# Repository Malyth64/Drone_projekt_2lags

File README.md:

# Drone_projekt_2lags
to lags ECS

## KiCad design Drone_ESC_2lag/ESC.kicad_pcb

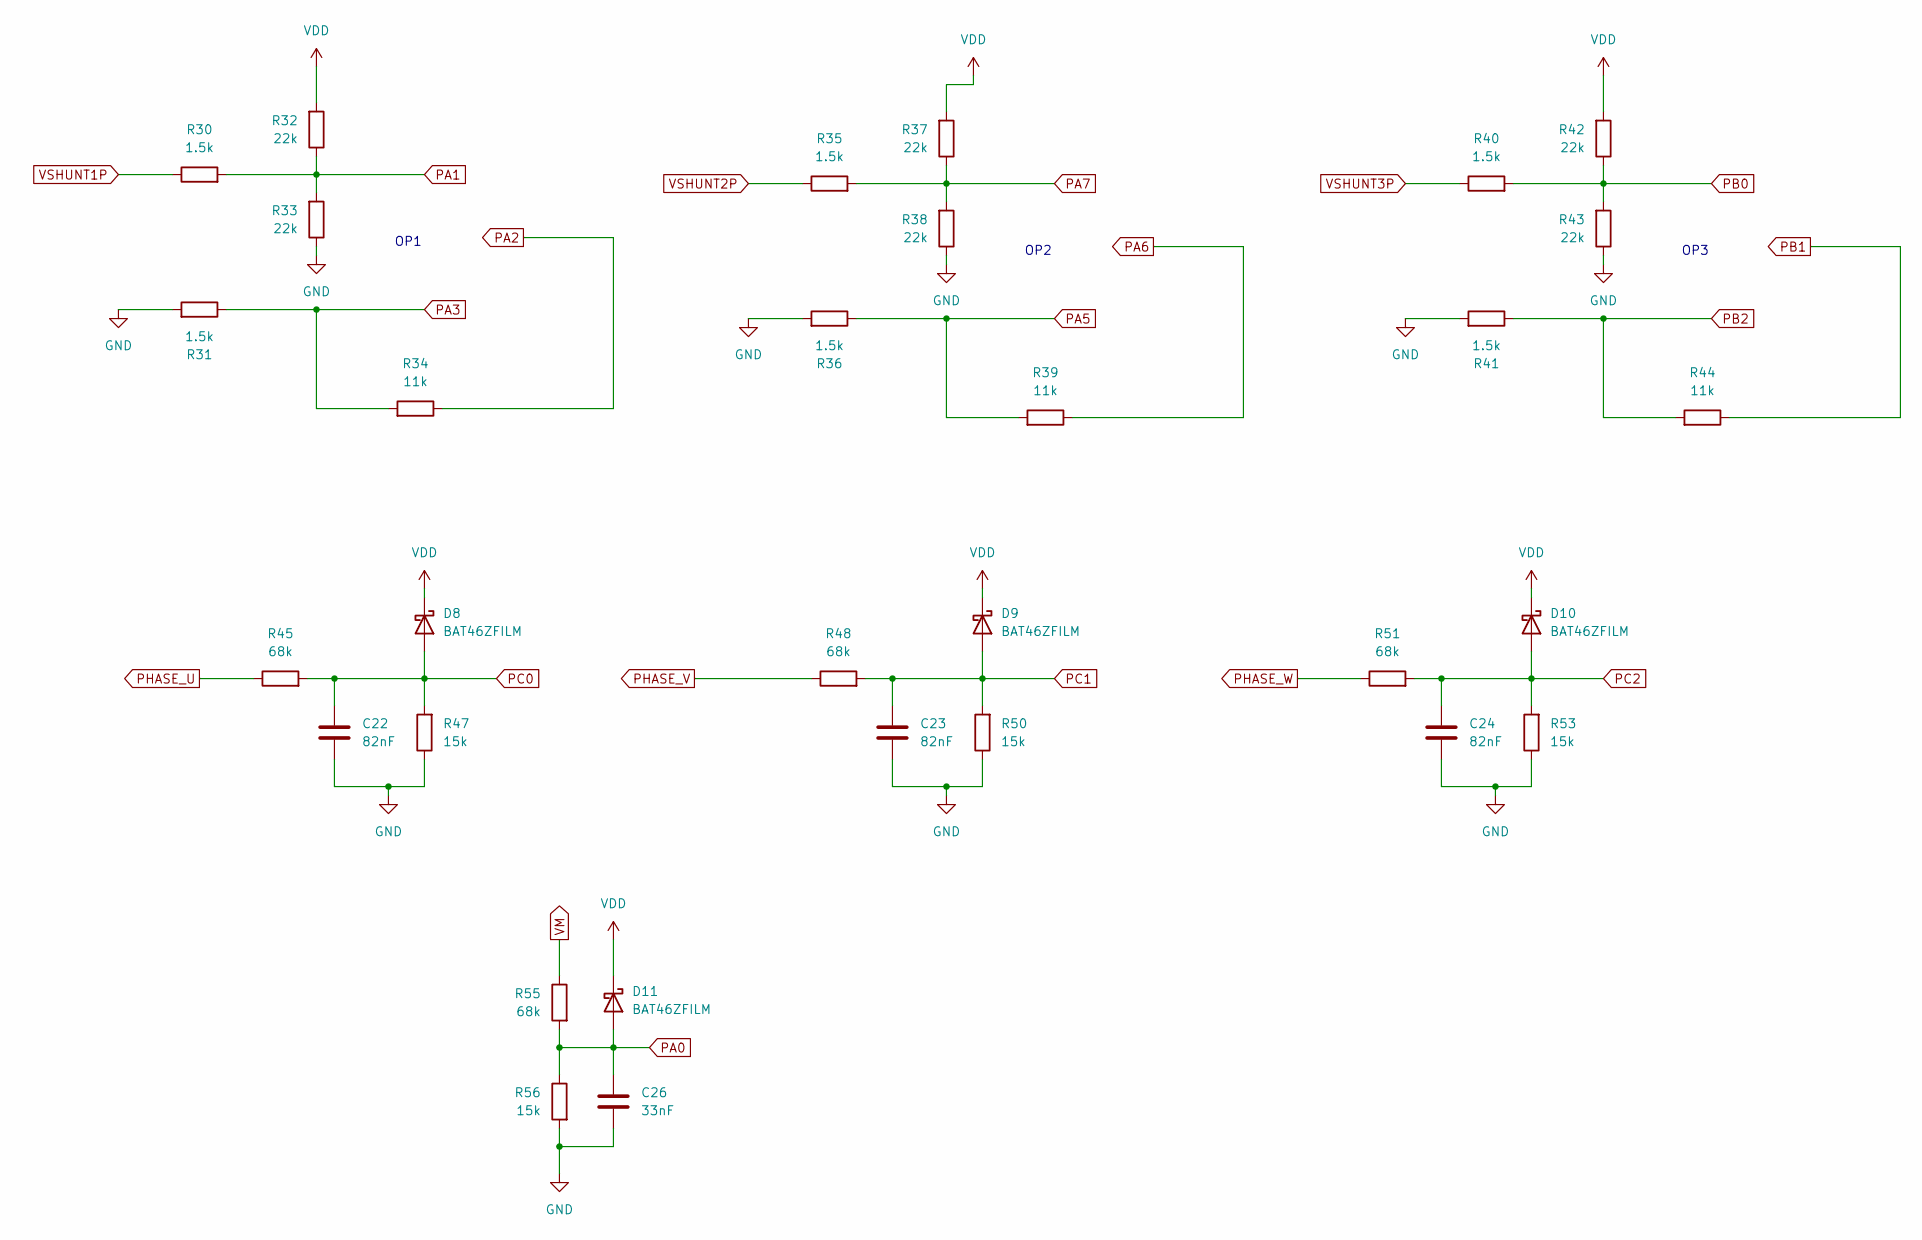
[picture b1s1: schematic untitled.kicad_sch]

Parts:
C22, C23, C24: 82nF; C_0805_2012Metric_Pad1.18x1.45mm_HandSolder
C26: 33nF; C_0805_2012Metric_Pad1.18x1.45mm_HandSolder
D8, D9, D10, D11: BAT46ZFILM; D_SOD-123
R30, R31, R35, R36, R40, R41: 1.5k; R_0805_2012Metric_Pad1.20x1.40mm_HandSolder
R32, R33, R37, R38, R42, R43: 22k; R_0805_2012Metric_Pad1.20x1.40mm_HandSolder
R34, R39, R44: 11k; R_0805_2012Metric_Pad1.20x1.40mm_HandSolder
R45, R48, R51: 68k; R_0805_2012Metric_Pad1.20x1.40mm_HandSolder
R47, R50, R53, R56: 15k; R_0805_2012Metric_Pad1.20x1.40mm_HandSolder
R55: 68k; R_0603_1608Metric_Pad0.98x0.95mm_HandSolder

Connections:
GND: C22.2, C23.2, C24.2, C26.2, R31.2, R33.1, R36.2, R38.1, R41.2, R43.1, R47.1, R50.1, R53.1, R56.2; also elsewhere on the board
PA0: C26.1, D11.2 (A), R55.2, R56.1; also elsewhere on the board
PA1: R30.2, R32.1, R33.2; also elsewhere on the board
PA2: R34.1; also elsewhere on the board
PA3: R31.1, R34.2; also elsewhere on the board
PA5: R36.1, R39.2; also elsewhere on the board
PA6: R39.1; also elsewhere on the board
PA7: R35.2, R37.1, R38.2; also elsewhere on the board
PB0: R40.2, R42.1, R43.2; also elsewhere on the board
PB1: R44.1; also elsewhere on the board
PB2: R41.1, R44.2; also elsewhere on the board
PC0: C22.1, D8.2 (A), R45.2, R47.2; also elsewhere on the board
PC1: C23.1, D9.2 (A), R48.2, R50.2; also elsewhere on the board
PC2: C24.1, D10.2 (A), R51.2, R53.2; also elsewhere on the board
PHASE_U: R45.1; also elsewhere on the board
PHASE_V: R48.1; also elsewhere on the board
PHASE_W: R51.1; also elsewhere on the board
VDD: D8.1 (K), D9.1 (K), D10.1 (K), D11.1 (K), R32.2, R37.2, R42.2; also elsewhere on the board
VM: R55.1; also elsewhere on the board
VSHUNT1P: R30.1; also elsewhere on the board
VSHUNT2P: R35.1; also elsewhere on the board
VSHUNT3P: R40.1; also elsewhere on the board

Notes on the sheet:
OP1
OP3
OP2

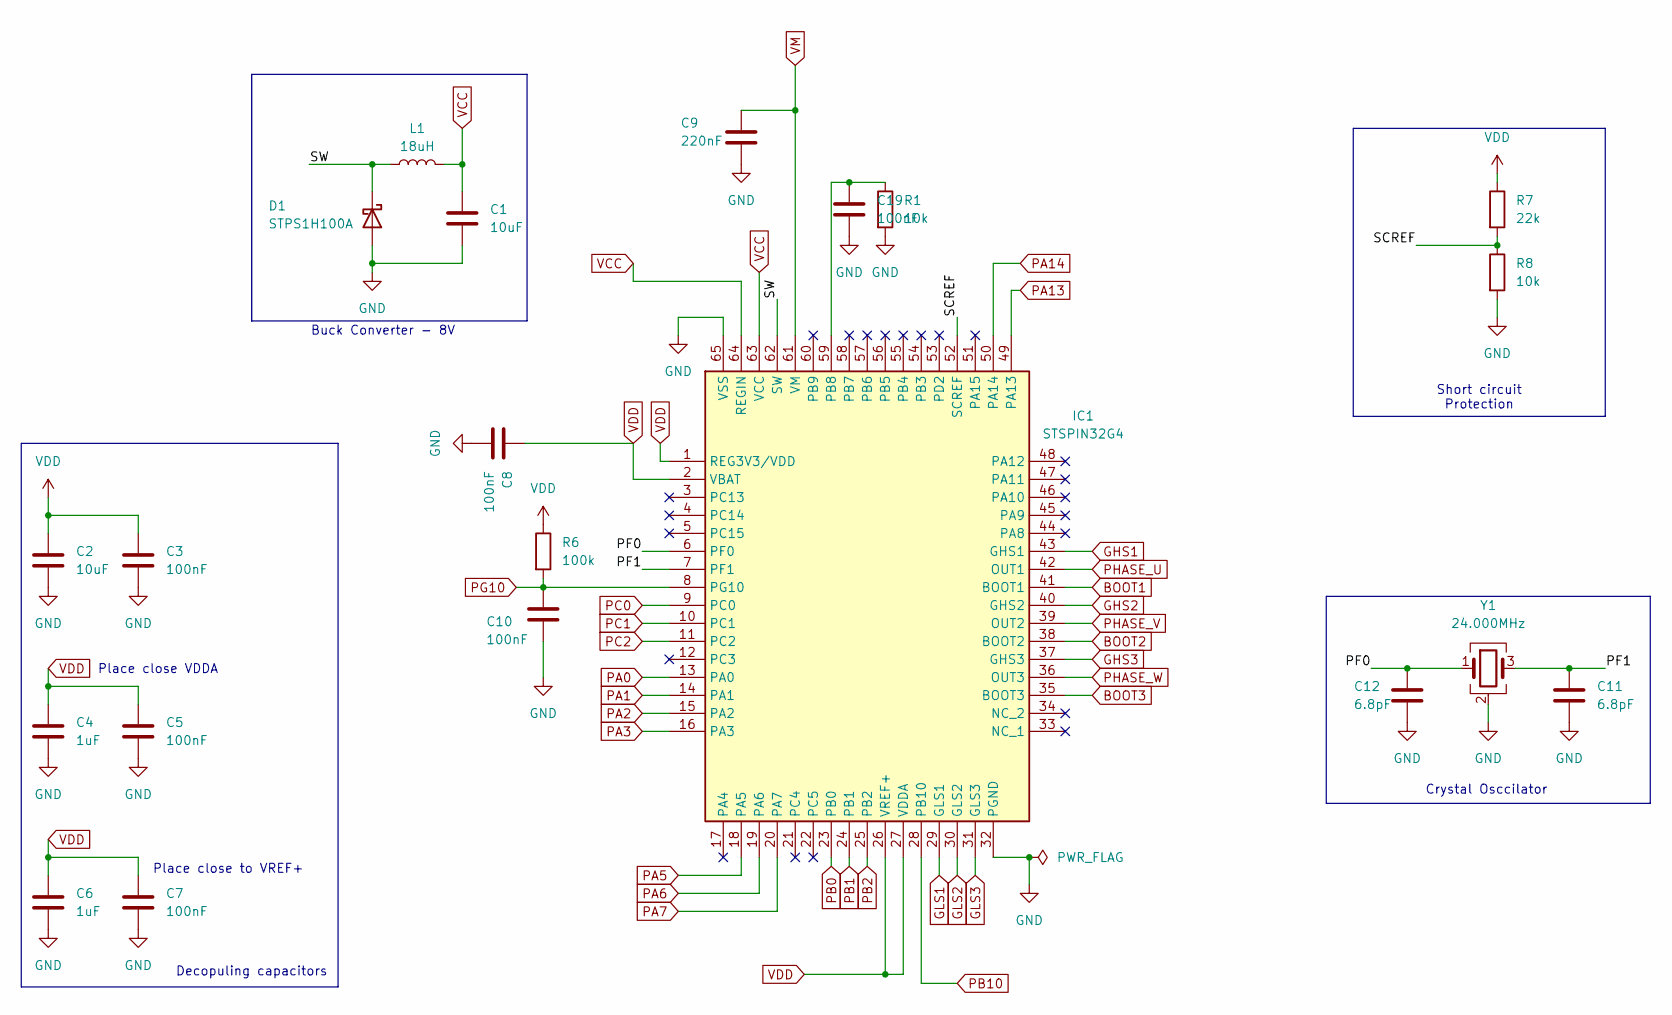
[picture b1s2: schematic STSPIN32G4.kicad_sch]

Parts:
C1, C2: 10uF; C_0805_2012Metric_Pad1.18x1.45mm_HandSolder
C3, C5, C7, C8, C10, C19: 100nF; C_0805_2012Metric_Pad1.18x1.45mm_HandSolder
C4, C6: 1uF; C_0805_2012Metric_Pad1.18x1.45mm_HandSolder
C9: 220nF; C_0805_2012Metric_Pad1.18x1.45mm_HandSolder
C11, C12: 6.8pF; C_0603_1608Metric_Pad1.08x0.95mm_HandSolder
D1: STPS1H100A; D_SMA-SMB_Universal_Handsoldering
IC1: STSPIN32G4; QFN50P900X900X100-65N-D; Mouser Part Number 511-STSPIN32G4
L1: 18uH; IND_ASPI-6045S_ABR
R1, R8: 10k; R_0805_2012Metric_Pad1.20x1.40mm_HandSolder
R6: 100k; R_0805_2012Metric_Pad1.20x1.40mm_HandSolder
R7: 22k; R_0805_2012Metric_Pad1.20x1.40mm_HandSolder
Y1: 24.000MHz; Crystal_SMD_2016-4Pin_2.0x1.6mm

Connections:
/STSPIN32G4 controller/PF0: C12.2, IC1.6 (PF0), Y1.1
/STSPIN32G4 controller/PF1: C11.1, IC1.7 (PF1), Y1.3
/STSPIN32G4 controller/SCREF: IC1.52 (SCREF), R7.2, R8.1
/STSPIN32G4 controller/SW: D1.1 (K), IC1.62 (SW), L1.1
BOOT1: IC1.41 (BOOT1); also elsewhere on the board
BOOT2: IC1.38 (BOOT2); also elsewhere on the board
BOOT3: IC1.35 (BOOT3); also elsewhere on the board
GHS1: IC1.43 (GHS1); also elsewhere on the board
GHS2: IC1.40 (GHS2); also elsewhere on the board
GHS3: IC1.37 (GHS3); also elsewhere on the board
GLS1: IC1.29 (GLS1); also elsewhere on the board
GLS2: IC1.30 (GLS2); also elsewhere on the board
GLS3: IC1.31 (GLS3); also elsewhere on the board
GND: C1.2, C2.2, C3.2, C4.2, C5.2, C6.2, C7.2, C8.2, C9.2, C10.1, C11.2, C12.1, C19.1, D1.2 (A), IC1.32 (PGND), IC1.65 (VSS), R1.2, R8.2, Y1.2 (G), Y1.4 (G); also elsewhere on the board
unnamed: C19.2, IC1.59 (PB8), R1.1
PA0: IC1.13 (PA0); also elsewhere on the board
PA1: IC1.14 (PA1); also elsewhere on the board
PA2: IC1.15 (PA2); also elsewhere on the board
PA3: IC1.16 (PA3); also elsewhere on the board
PA5: IC1.18 (PA5); also elsewhere on the board
PA6: IC1.19 (PA6); also elsewhere on the board
PA7: IC1.20 (PA7); also elsewhere on the board
PA13: IC1.49 (PA13); also elsewhere on the board
PA14: IC1.50 (PA14); also elsewhere on the board
PB0: IC1.23 (PB0); also elsewhere on the board
PB1: IC1.24 (PB1); also elsewhere on the board
PB2: IC1.25 (PB2); also elsewhere on the board
PB10: IC1.28 (PB10); also elsewhere on the board
PC0: IC1.9 (PC0); also elsewhere on the board
PC1: IC1.10 (PC1); also elsewhere on the board
PC2: IC1.11 (PC2); also elsewhere on the board
PG10: C10.2, IC1.8 (PG10), R6.2
PHASE_U: IC1.42 (OUT1); also elsewhere on the board
PHASE_V: IC1.39 (OUT2); also elsewhere on the board
PHASE_W: IC1.36 (OUT3); also elsewhere on the board
VCC: C1.1, IC1.63 (VCC), IC1.64 (REGIN), L1.2
VDD: C2.1, C3.1, C4.1, C5.1, C6.1, C7.1, C8.1, IC1.1 (REG3V3/VDD), IC1.2 (VBAT), IC1.26 (VREF+), IC1.27 (VDDA), R6.1, R7.1; also elsewhere on the board
VM: C9.1, IC1.61 (VM); also elsewhere on the board

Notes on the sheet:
Short circuit Protection
Place close VDDA
Place close to VREF+
Buck Converter - 8V
Decopuling capacitors
Crystal Osccilator

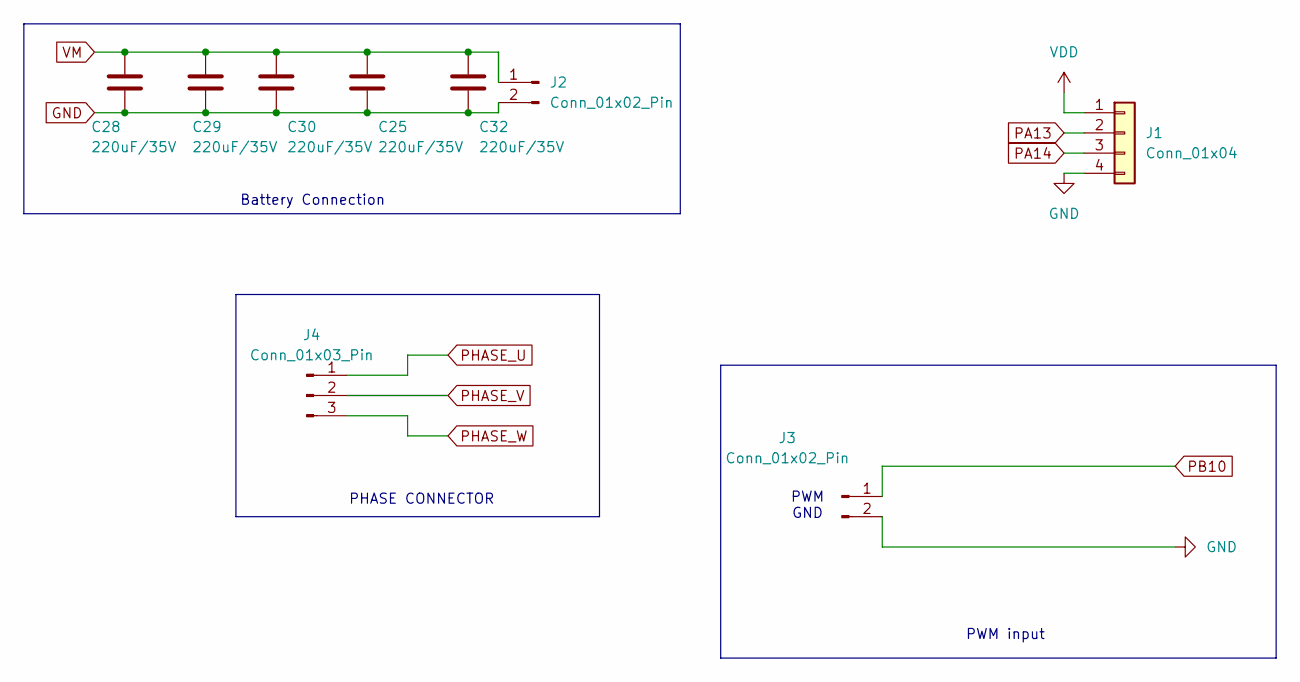
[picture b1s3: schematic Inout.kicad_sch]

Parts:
C25, C28, C29, C30, C32: 220uF/35V; C_Radial_D8.0mm_H11.5mm_P3.50mm
J1: Conn_01x04; PinHeader_1x04_P2.54mm_Vertical
J2: Conn_01x02_Pin; Solderpad_VM_GND
J3: Conn_01x02_Pin; Soderpad_PWM
J4: Conn_01x03_Pin; Solderpad_High_current

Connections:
GND: C25.2, C28.2, C29.2, C30.2, C32.2, J1.4, J2.2, J3.2; also elsewhere on the board
PA13: J1.2; also elsewhere on the board
PA14: J1.3; also elsewhere on the board
PB10: J3.1; also elsewhere on the board
PHASE_U: J4.1; also elsewhere on the board
PHASE_V: J4.2; also elsewhere on the board
PHASE_W: J4.3; also elsewhere on the board
VDD: J1.1; also elsewhere on the board
VM: C25.1, C28.1, C29.1, C30.1, C32.1, J2.1; also elsewhere on the board

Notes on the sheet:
PWM input
PHASE CONNECTOR
PWM GND
Battery Connection

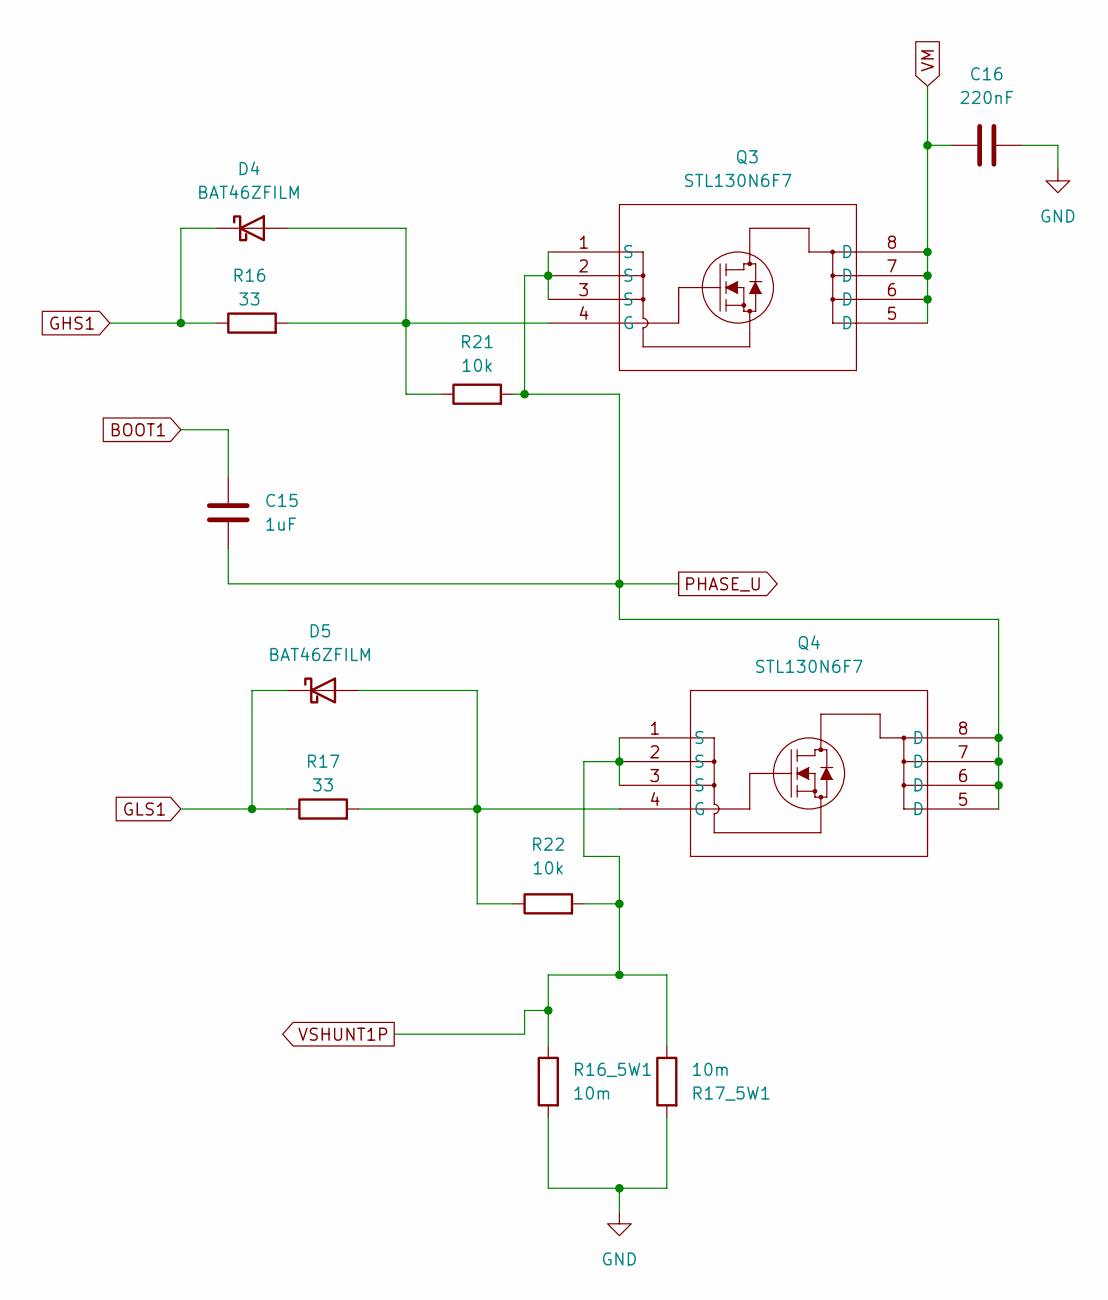
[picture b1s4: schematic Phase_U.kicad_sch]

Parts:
C15: 1uF; C_0805_2012Metric_Pad1.18x1.45mm_HandSolder
C16: 220nF; C_0805_2012Metric_Pad1.18x1.45mm_HandSolder
D4, D5: BAT46ZFILM; D_SOD-123
Q3, Q4: STL130N6F7; POWERFLAT_5X6_C_STM-L
R16, R17: 33; R_0805_2012Metric_Pad1.20x1.40mm_HandSolder
R16_5W1, R17_5W1: 10m; RES_WSHP2818R0100FEA
R21, R22: 10k; R_0805_2012Metric_Pad1.20x1.40mm_HandSolder

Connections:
BOOT1: C15.1; also elsewhere on the board
GHS1: D4.1 (K), R16.1; also elsewhere on the board
GLS1: D5.1 (K), R17.1; also elsewhere on the board
GND: C16.2, R16_5W1.2, R17_5W1.2; also elsewhere on the board
unnamed: D4.2 (A), Q3.4 (G), R16.2, R21.1
unnamed: D5.2 (A), Q4.4 (G), R17.2, R22.1
PHASE_U: C15.2, Q3.1 (S), Q3.2 (S), Q3.3 (S), Q4.5 (D), Q4.6 (D), Q4.7 (D), Q4.8 (D), R21.2; also elsewhere on the board
VM: C16.1, Q3.5 (D), Q3.6 (D), Q3.7 (D), Q3.8 (D); also elsewhere on the board
VSHUNT1P: Q4.1 (S), Q4.2 (S), Q4.3 (S), R16_5W1.1, R17_5W1.1, R22.2; also elsewhere on the board

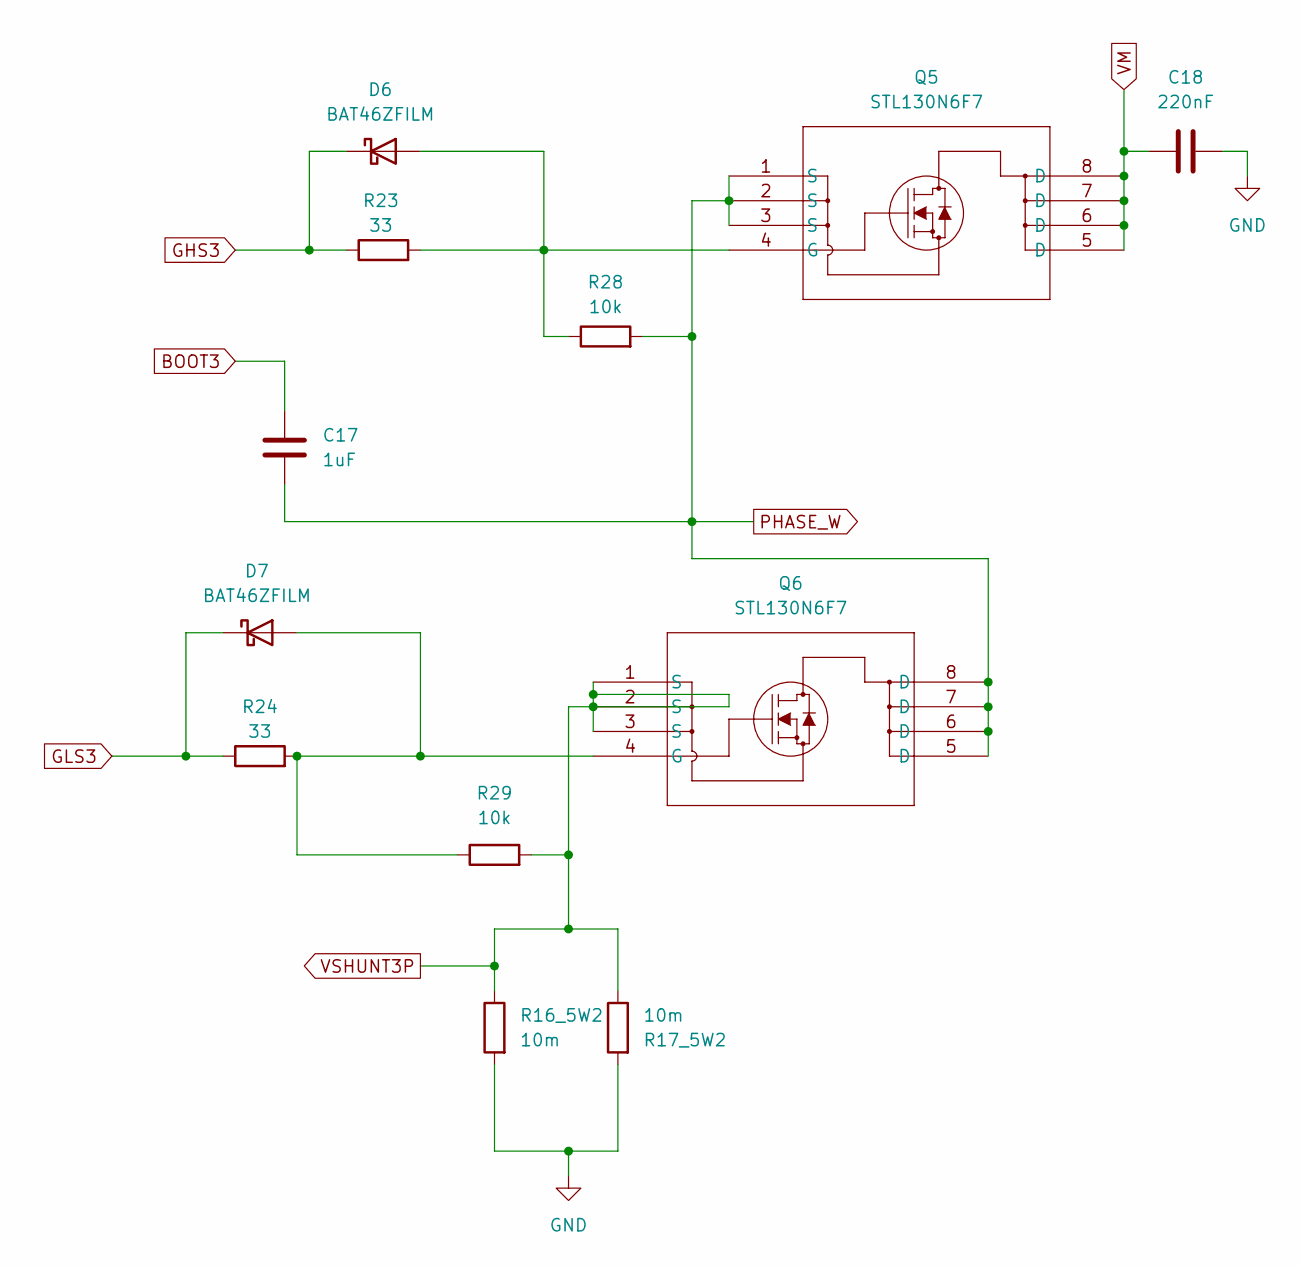
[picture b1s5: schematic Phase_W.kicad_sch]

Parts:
C17: 1uF; C_0805_2012Metric_Pad1.18x1.45mm_HandSolder
C18: 220nF; C_0805_2012Metric_Pad1.18x1.45mm_HandSolder
D6, D7: BAT46ZFILM; D_SOD-123
Q5, Q6: STL130N6F7; POWERFLAT_5X6_C_STM-L
R16_5W2, R17_5W2: 10m; RES_WSHP2818R0100FEA
R23, R24: 33; R_0805_2012Metric_Pad1.20x1.40mm_HandSolder
R28, R29: 10k; R_0805_2012Metric_Pad1.20x1.40mm_HandSolder

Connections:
BOOT3: C17.1; also elsewhere on the board
GHS3: D6.1 (K), R23.1; also elsewhere on the board
GLS3: D7.1 (K), R24.1; also elsewhere on the board
GND: C18.2, R16_5W2.2, R17_5W2.2; also elsewhere on the board
unnamed: D6.2 (A), Q5.4 (G), R23.2, R28.1
unnamed: D7.2 (A), Q6.4 (G), R24.2, R29.1
PHASE_W: C17.2, Q5.1 (S), Q5.2 (S), Q5.3 (S), Q6.5 (D), Q6.6 (D), Q6.7 (D), Q6.8 (D), R28.2; also elsewhere on the board
VM: C18.1, Q5.5 (D), Q5.6 (D), Q5.7 (D), Q5.8 (D); also elsewhere on the board
VSHUNT3P: Q6.1 (S), Q6.2 (S), Q6.3 (S), R16_5W2.1, R17_5W2.1, R29.2; also elsewhere on the board

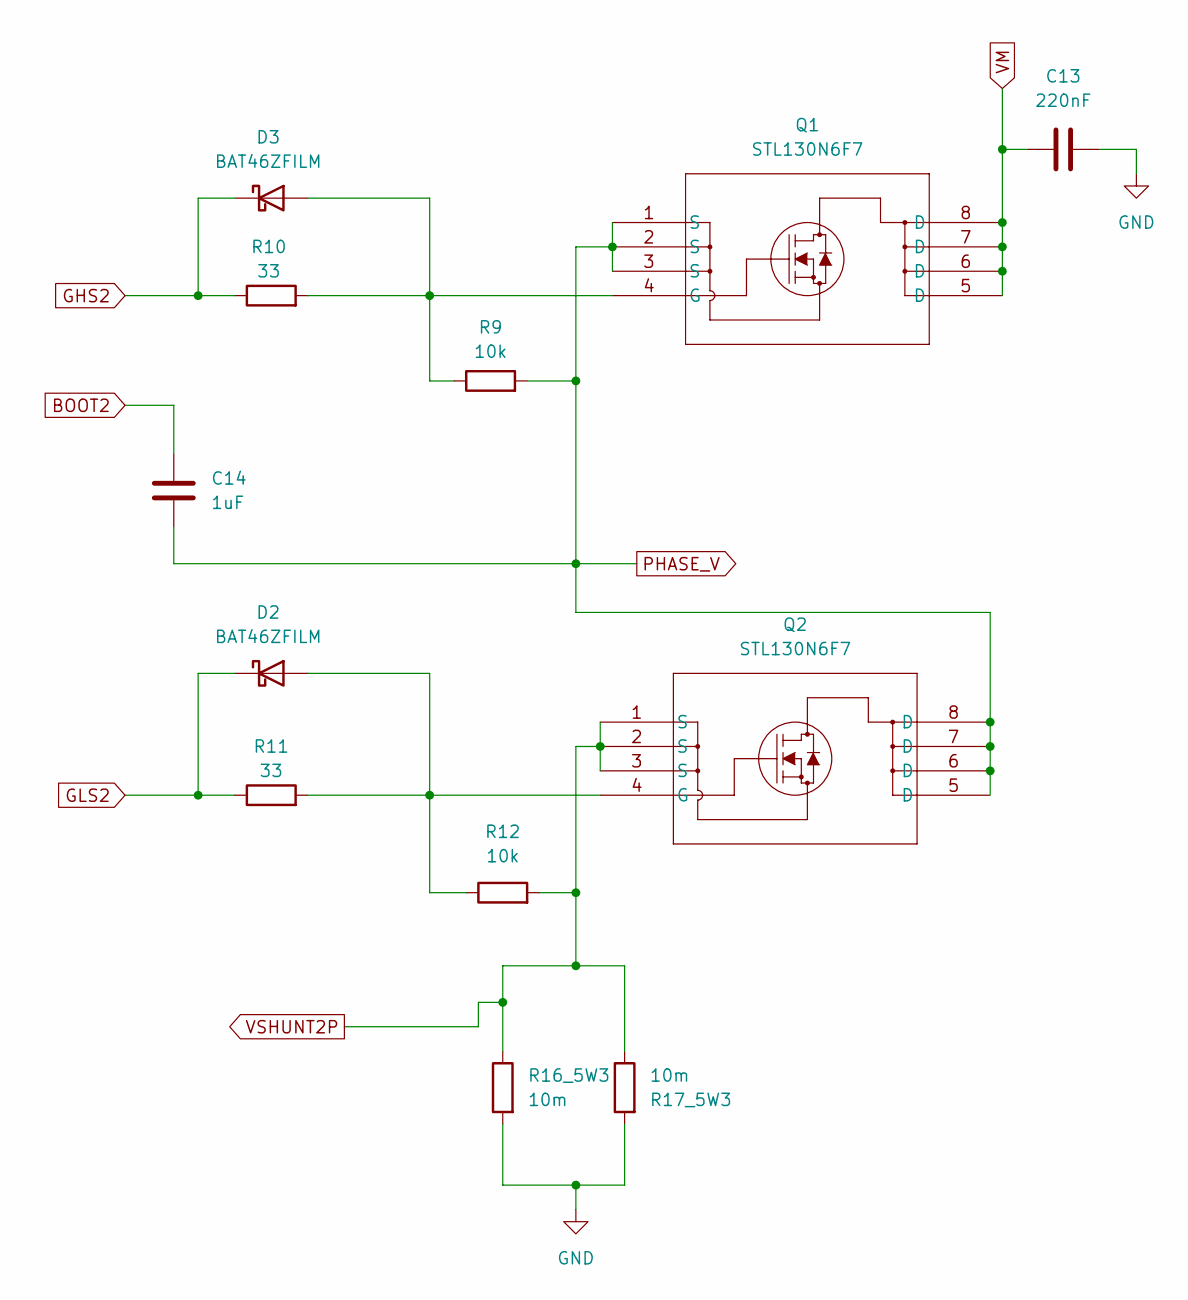
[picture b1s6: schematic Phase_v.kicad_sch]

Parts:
C13: 220nF; C_0805_2012Metric_Pad1.18x1.45mm_HandSolder
C14: 1uF; C_0805_2012Metric_Pad1.18x1.45mm_HandSolder
D2, D3: BAT46ZFILM; D_SOD-123
Q1, Q2: STL130N6F7; POWERFLAT_5X6_C_STM-L
R9, R12: 10k; R_0805_2012Metric_Pad1.20x1.40mm_HandSolder
R10, R11: 33; R_0805_2012Metric_Pad1.20x1.40mm_HandSolder
R16_5W3, R17_5W3: 10m; RES_WSHP2818R0100FEA

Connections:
BOOT2: C14.1; also elsewhere on the board
GHS2: D3.1 (K), R10.1; also elsewhere on the board
GLS2: D2.1 (K), R11.1; also elsewhere on the board
GND: C13.2, R16_5W3.2, R17_5W3.2; also elsewhere on the board
unnamed: D2.2 (A), Q2.4 (G), R11.2, R12.1
unnamed: D3.2 (A), Q1.4 (G), R9.1, R10.2
PHASE_V: C14.2, Q1.1 (S), Q1.2 (S), Q1.3 (S), Q2.5 (D), Q2.6 (D), Q2.7 (D), Q2.8 (D), R9.2; also elsewhere on the board
VM: C13.1, Q1.5 (D), Q1.6 (D), Q1.7 (D), Q1.8 (D); also elsewhere on the board
VSHUNT2P: Q2.1 (S), Q2.2 (S), Q2.3 (S), R12.2, R16_5W3.1, R17_5W3.1; also elsewhere on the board

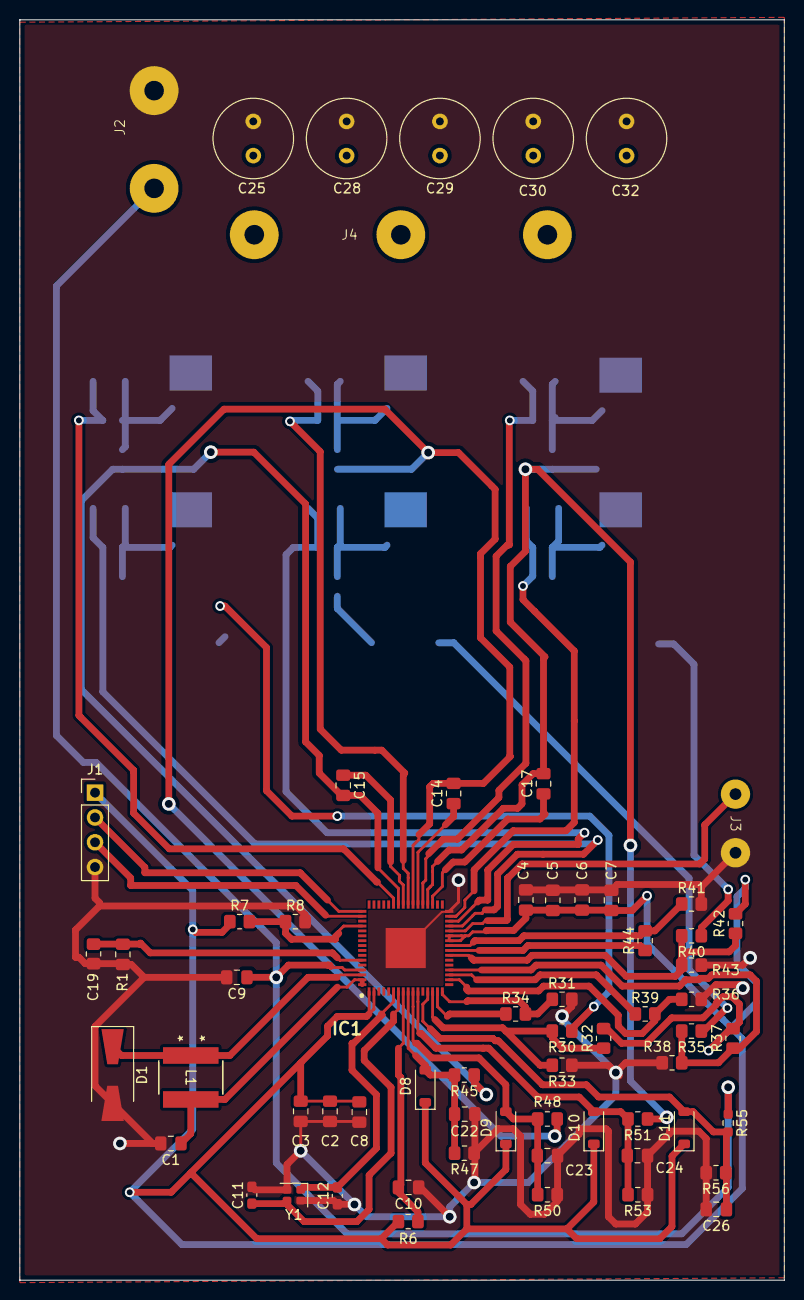
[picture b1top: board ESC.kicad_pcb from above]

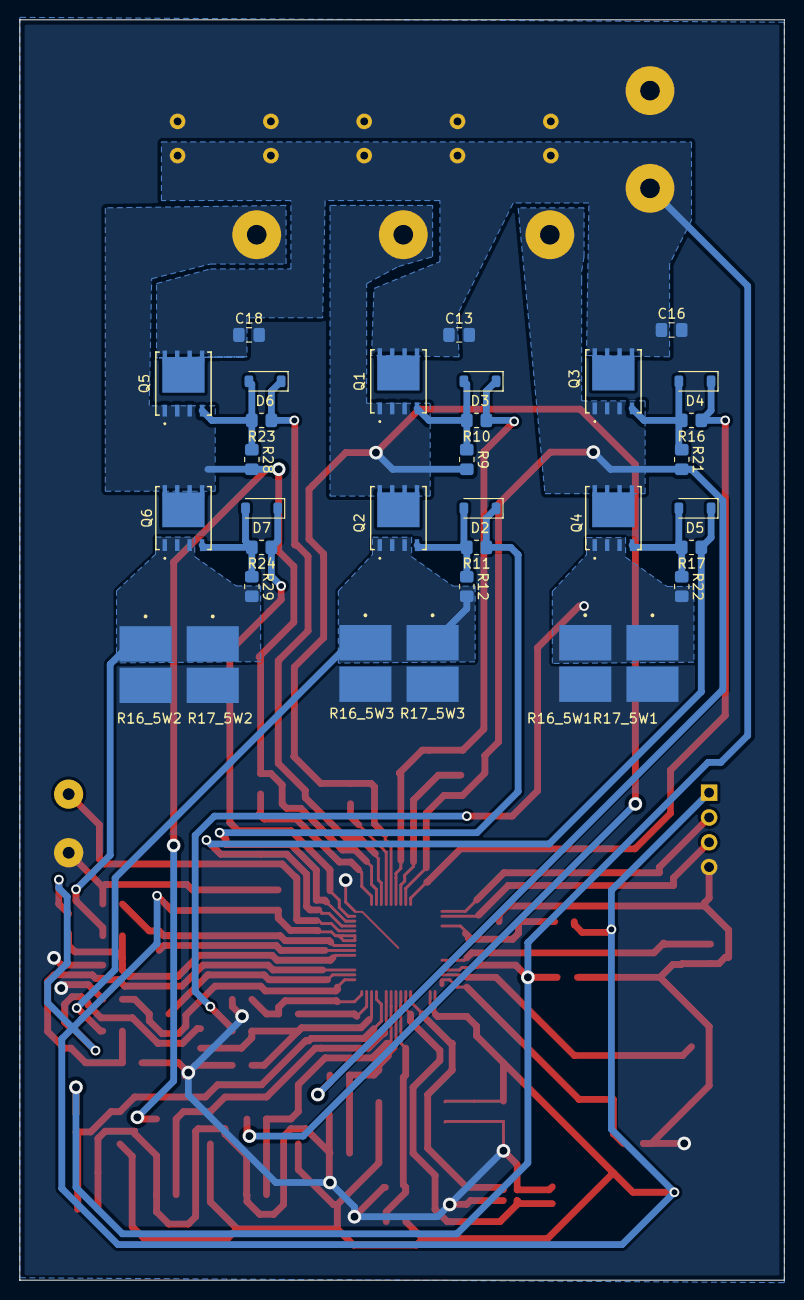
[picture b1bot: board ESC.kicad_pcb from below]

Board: 2 copper layers, 78.2 x 129.0 mm, 97 parts (33 on the bottom side), 47 nets.

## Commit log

2026-05-13 Add .gitignore for KiCad and OS files
2026-05-13 nyt to lags design
2026-05-13 delt igennem VS
2026-05-15 Næsten færdig med PCB, retter fejl
2026-05-15 Færdig PCB burde det være
